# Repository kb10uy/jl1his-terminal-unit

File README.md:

# JL1HIS Terminal Unit

Raspberry Pi Pico 2 を採用した RTTY ターミナルユニット

## 設計方針

なぜ作るかといえば USB Serial では DTR/RTS の bit-bang は精度に限界があるからなので、**キーイングを USB からのデータで直接行わない**のを原則とする。

- PC からは USB Serial と USB Audio の組として見える
- USB Serial はコマンドを送受信するものであり、直接キーイングしたり送信するデータを受け取ることはしない
- RP2350 の使えそうな機能は積極的に使う(特に PIO)
- 接続するリグを問わない回路設計

## アナログ回路

回り込みを防ぐためにリグ側とホスト PC 側はグランド分離する。AF 入力はインピーダンス 10kΩ・数百mV(p-p) を想定している。

## コマンド制御

[docs/control-port.md](./docs/control-port.md) を参照

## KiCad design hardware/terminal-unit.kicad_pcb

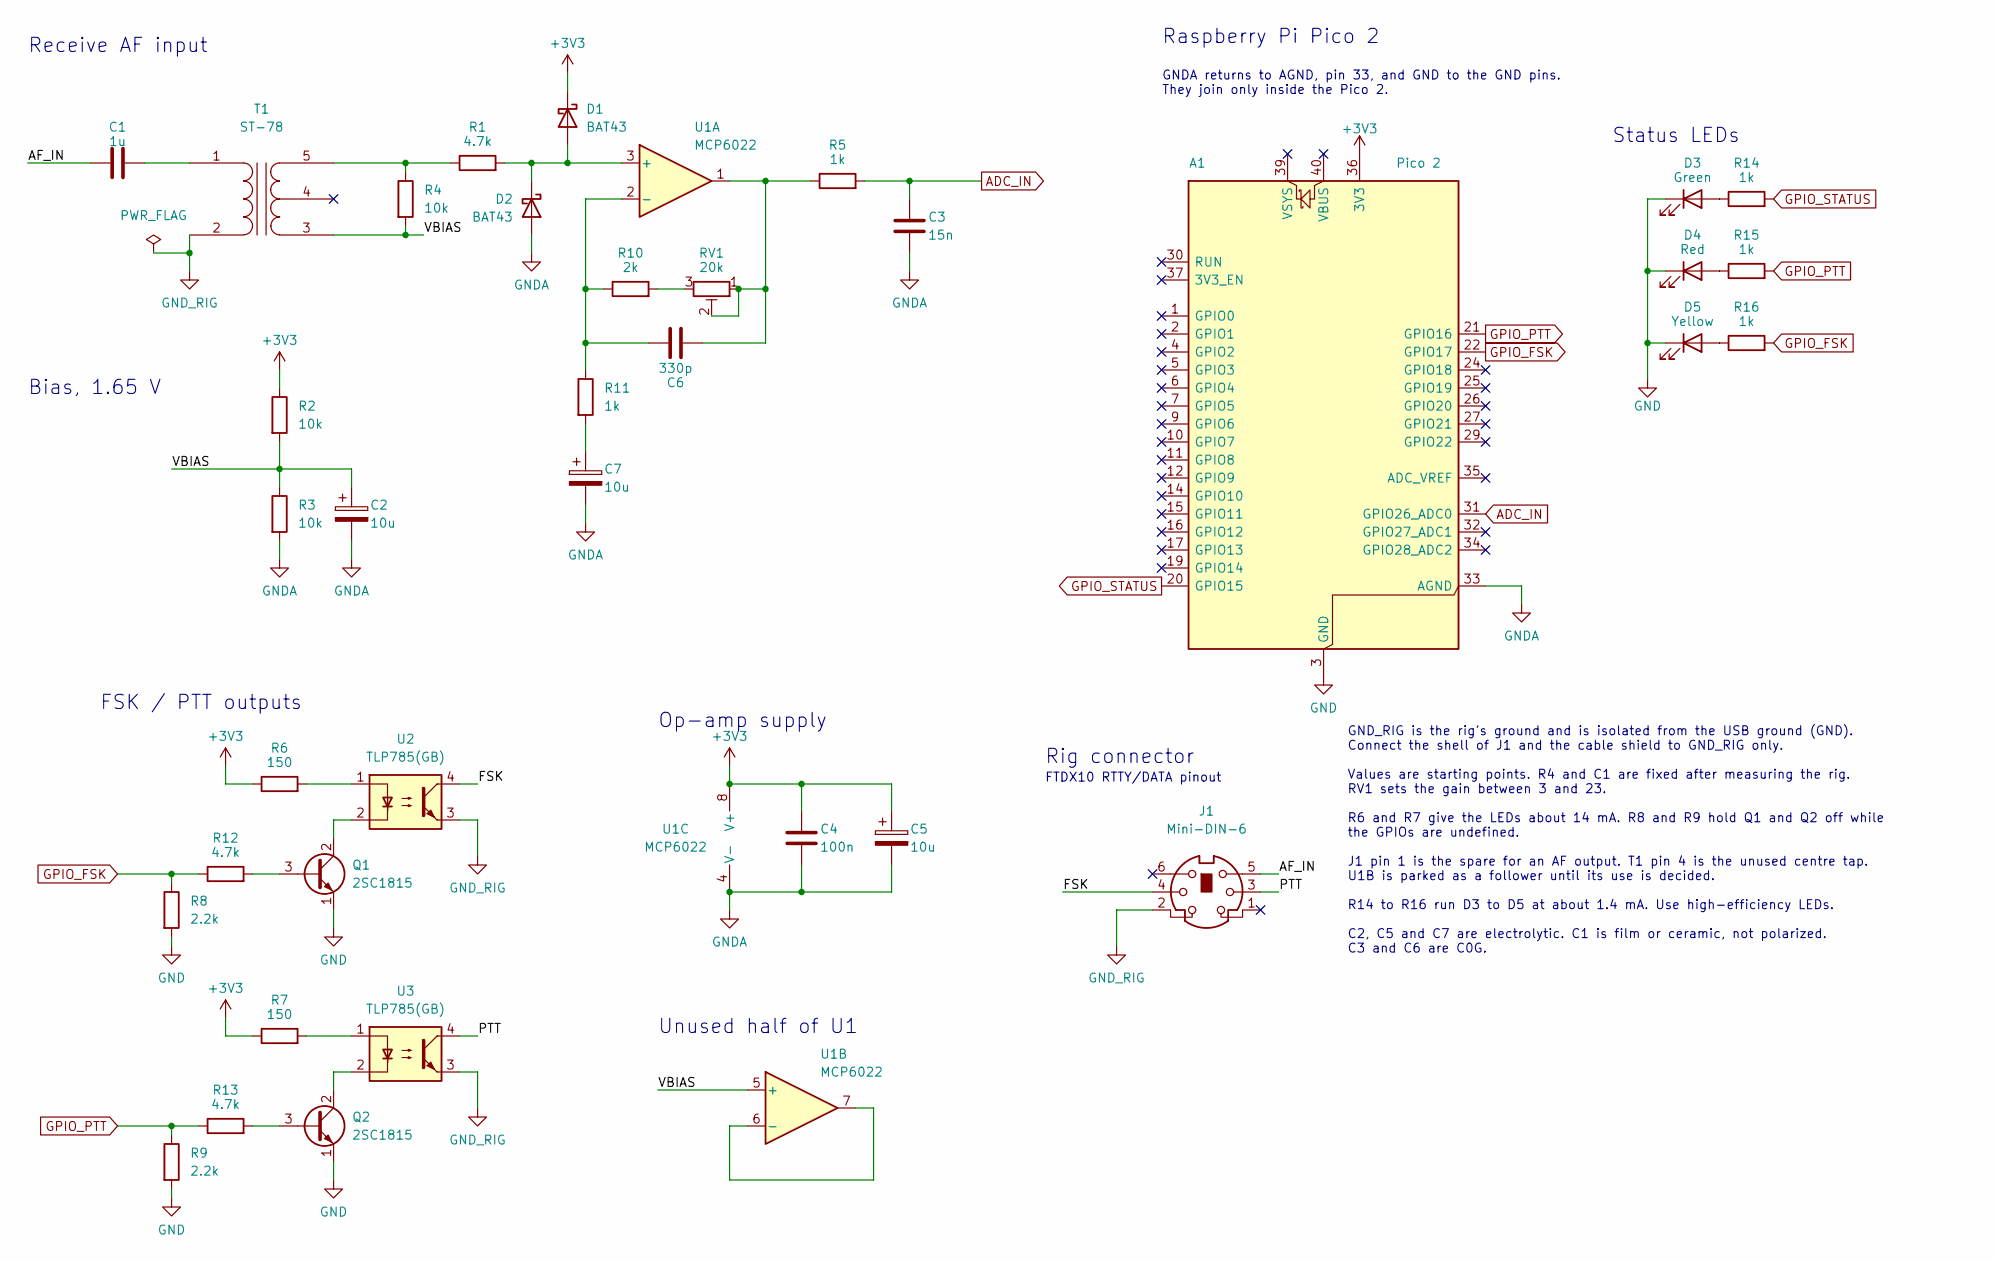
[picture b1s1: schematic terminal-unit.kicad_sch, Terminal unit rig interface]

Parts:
A1: Pico 2; RaspberryPi_Pico_Common_THT
C1: 1u; C_Rect_L7.2mm_W2.5mm_P5.00mm
C2, C5, C7: 10u; CP_Radial_D5.0mm_P2.50mm
C3: 15n; C_Rect_L7.2mm_W2.5mm_P5.00mm
C4: 100n; C_Disc_D5.0mm_W2.5mm_P2.50mm
C6: 330p; C_Disc_D5.0mm_W2.5mm_P2.50mm
D1: BAT43; D_DO-35_SOD27_P12.70mm_Horizontal
D2: BAT43; D_DO-35_SOD27_P7.62mm_Horizontal
D3: Green; LED_D3.0mm
D4: Red; LED_D3.0mm
D5: Yellow; LED_D3.0mm
J1: Mini-DIN-6; MiniDIN6_Breakout_SIP8
Q1, Q2: 2SC1815; TO-92_Inline_Wide
R1, R12, R13: 4.7k; R_Axial_DIN0207_L6.3mm_D2.5mm_P10.16mm_Horizontal
R2, R3, R4: 10k; R_Axial_DIN0207_L6.3mm_D2.5mm_P10.16mm_Horizontal
R5, R11, R14, R15, R16: 1k; R_Axial_DIN0207_L6.3mm_D2.5mm_P10.16mm_Horizontal
R6, R7: 150; R_Axial_DIN0207_L6.3mm_D2.5mm_P10.16mm_Horizontal
R8, R9: 2.2k; R_Axial_DIN0207_L6.3mm_D2.5mm_P10.16mm_Horizontal
R10: 2k; R_Axial_DIN0207_L6.3mm_D2.5mm_P10.16mm_Horizontal
RV1: 20k; Potentiometer_Bourns_3296W_Vertical
T1: ST-78; ST-78_Leads_Perfboard
U1: MCP6022; DIP-8_W7.62mm
U2, U3: TLP785(GB); DIP-4_W7.62mm

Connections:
+3V3: A1.36 (3V3), C4.1, C5.1, D1.1 (K), R2.1, R6.1, R7.1, U1.8 (V+)
/AF_IN: C1.1, J1.5
/FSK: J1.4, U2.4
/PTT: J1.3, U3.4
/VBIAS: C2.1, R2.2, R3.1, R4.2, T1.3 (SA), U1.5 (+)
ADC_IN: A1.31 (GPIO26_ADC0), C3.1, R5.2
GND: A1.3 (GND), A1.8 (GND), A1.13 (GND), A1.18 (GND), A1.23 (GND), A1.28 (GND), A1.38 (GND), D3.1 (K), D4.1 (K), D5.1 (K), Q1.1 (E), Q2.1 (E), R8.2, R9.2
GNDA: A1.33 (AGND), C2.2, C3.2, C4.2, C5.2, C7.2, D2.2 (A), R3.2, U1.4 (V-)
GND_RIG: J1.2, T1.2 (AB), U2.3, U3.3
GPIO_FSK: A1.22 (GPIO17), R8.1, R12.1, R16.2
GPIO_PTT: A1.21 (GPIO16), R9.1, R13.1, R15.2
GPIO_STATUS: A1.20 (GPIO15), R14.2
unnamed: C6.2, R5.1, RV1.1, RV1.2, U1.1
unnamed: C7.1, R11.2
unnamed: D1.2 (A), D2.1 (K), R1.2, U1.3 (+)
unnamed: D3.2 (A), R14.1
unnamed: D4.2 (A), R15.1
unnamed: D5.2 (A), R16.1
unnamed: Q1.3 (B), R12.2
unnamed: Q1.2 (C), U2.2
unnamed: Q2.3 (B), R13.2
unnamed: Q2.2 (C), U3.2
unnamed: R6.2, U2.1
unnamed: R7.2, U3.1
unnamed: R10.2, RV1.3
unnamed: C1.2, T1.1 (AA)
unnamed: R1.1, R4.1, T1.5 (SB)
unnamed: C6.1, R10.1, R11.1, U1.2 (-)
unnamed: U1.6 (-), U1.7

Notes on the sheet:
Rig connector
GNDA returns to AGND, pin 33, and GND to the GND pins. They join only inside the Pico 2.
GND_RIG is the rig's ground and is isolated from the USB ground (GND). Connect the shell of J1 and the cable shield to GND_RIG only. Values are starting points. R4 and C1 are fixed after measuring the rig. RV1 sets the gain between 3 and 23. R6 and R7 give the LEDs about 14 mA. R8 and R9 hold Q1 an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
FTDX10 RTTY/DATA pinout
Unused half of U1
Receive AF input
Bias, 1.65 V
Raspberry Pi Pico 2
FSK / PTT outputs
Op-amp supply
Status LEDs

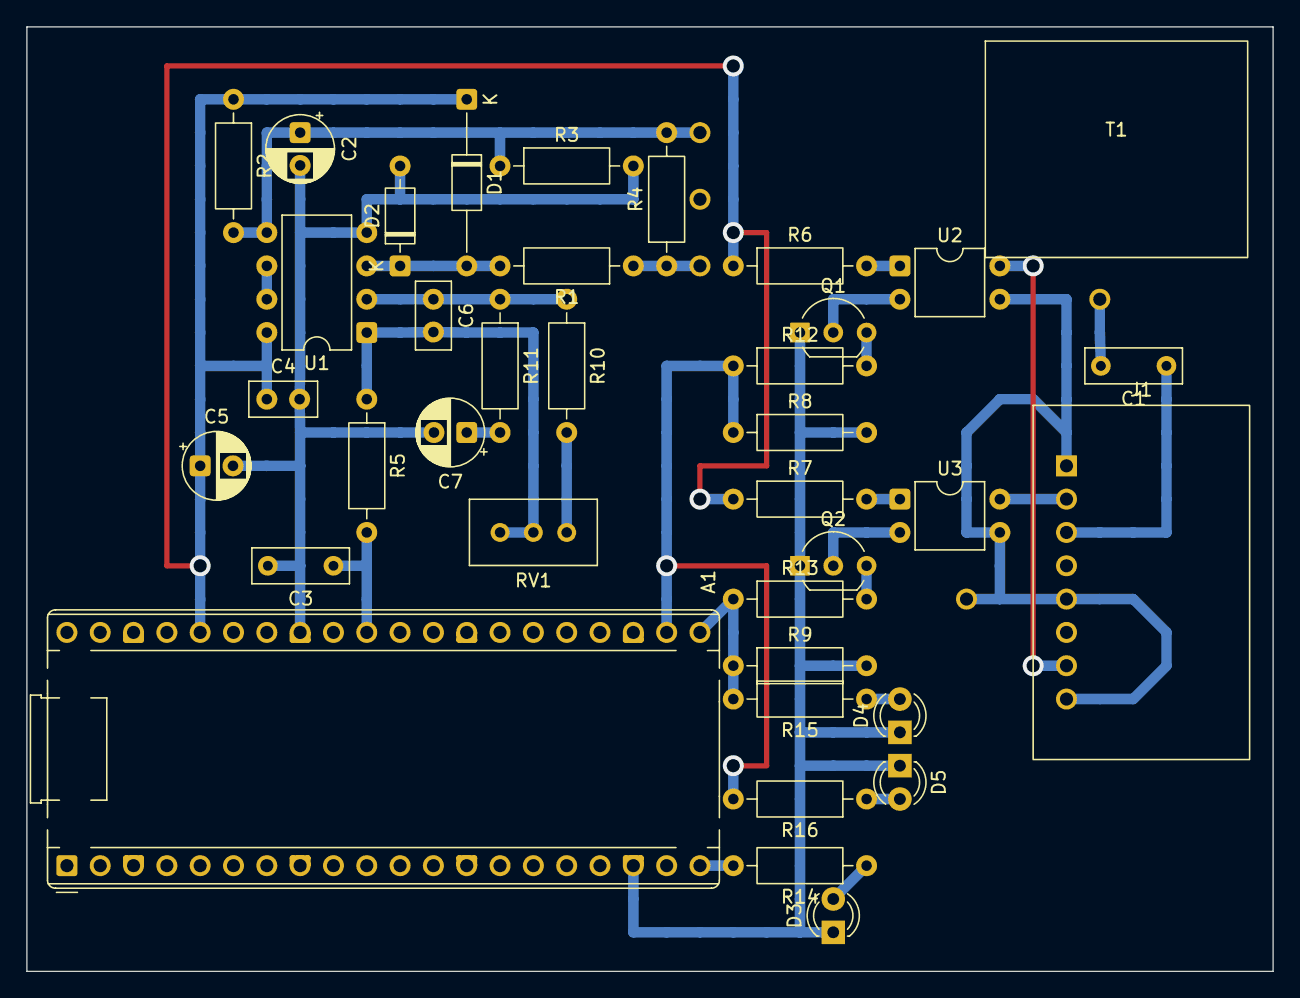
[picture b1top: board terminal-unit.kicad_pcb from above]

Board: 2 copper layers, 95.0 x 72.0 mm, 37 parts (0 on the bottom side), 29 nets.
